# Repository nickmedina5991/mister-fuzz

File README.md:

# Mister Fuzz - Silicon Fuzz Face Guitar Pedal

A silicon Fuzz Face guitar effects pedal designed end-to-end:
LTSpice simulation, breadboard prototype, custom KiCad PCB, and a
custom Fusion 360 enclosure.

## What this is

A classic Fuzz Face circuit rebuilt with modern 2N3904 NPN silicon
transistors instead of the original 1960s germanium PNPs. The substitution
required re-deriving the bias network for silicon's higher hFE, since the
original 8.2kΩ bias resistor leaves Q2's collector at the wrong operating
point with modern transistors. The production design uses a 10kΩ trim pot
in place of the fixed resistor, so each build can be tuned to the specific
2N3904s installed.

## Features

- 9V battery or 2.1mm DC barrel jack power, with automatic switchover
- TRS input jack that disconnects the battery when no cable is plugged in
- 1N4001 reverse-polarity protection diode
- 47µF supply decoupling capacitor
- 3PDT true-bypass switching with LED indicator
- 10kΩ bias trimmer (set Q2 collector to 4.5V during assembly)
- 500kΩ audio-taper volume control
- 1kΩ linear fuzz control
- Two-layer PCB with stitched ground pour for low-noise high-gain operation

## Repo layout

- `simulation/` contains the LTSpice schematic and plots from the analysis
- `hardware/` contains the KiCad project, schematic and PCB exports, Gerbers, and BOM
- `docs/` contains the design notes and bias tuning instructions
- `enclosure/` will contain the Fusion 360 enclosure model and drill template (coming soon)

## Design highlights

The full design walkthrough lives in [`docs/design-notes.md`](docs/design-notes.md).
Some of the more interesting findings:

- **The silicon variant required ~6kΩ bias resistance instead of the original
  8.2kΩ.** A parametric LTSpice sweep of R3 from 2kΩ to 10kΩ identified the
  value that lands Q2's collector at the target 4.5V with modern 2N3904s.
- **The circuit has approximately 62dB of peak passband gain.** At realistic
  guitar signal levels (~200mV), the pedal saturates fully at any fuzz setting
  above the lowest 10% of the pot's range. This is why the Fuzz Face cleans
  up so dramatically when you roll back the guitar's volume knob.
- **The fuzz control sculpts EQ, not just gain.** At maximum fuzz, the
  response shows a resonant peak at 115Hz (in the guitar's low fundamental
  range). At minimum fuzz, the response flattens into a near-clean wideband
  amplifier. The pot changes both gain and tonal character simultaneously.
- **Simulation results match published ElectroSmash reference data** within
  the expected silicon-vs-germanium tolerances. The silicon variant has a
  slightly higher low-frequency corner (~50-80Hz vs 14Hz for germanium),
  which matches the documented "less bass" character of silicon Fuzz Faces.

## Build

1. Order parts per `hardware/bom.csv`.
2. Send `hardware/gerbers/mister-fuzz-gerbers.zip` to a PCB fab house
   (JLCPCB, PCBWay, OSH Park, etc.).
3. Hand-solder all through-hole components.
4. Wire the panel-mounted parts (audio jacks, footswitch, DC jack, LED)
   to the PCB pad headers using hookup wire.
5. Set the bias trim pot per [`docs/bias-tuning.md`](docs/bias-tuning.md).
6. Install in the enclosure and play.

## License

MIT. See [`LICENSE`](LICENSE) for details. You're free to use, modify,
build, and sell this design with attribution.

## Acknowledgments

- ElectroSmash's Fuzz Face analysis at
  [electrosmash.com/fuzz-face](https://www.electrosmash.com/fuzz-face)
  for the canonical reference data this design was verified against.
- R.G. Keen's "The Technology of the Fuzz Face" on GEOFEX for the
  background on bias sensitivity and transistor selection.
- Barbarach's website and tutorials on designing and building a 
  Fuzz Face clone (https://barbarach.com/articles/building-a-fuzz-face-clone/)
- Dallas Arbiter and the original 1966 Fuzz Face designers, whose
  deceptively simple two-transistor circuit has kept guitarists and
  electronics hobbyists busy for nearly 60 years.

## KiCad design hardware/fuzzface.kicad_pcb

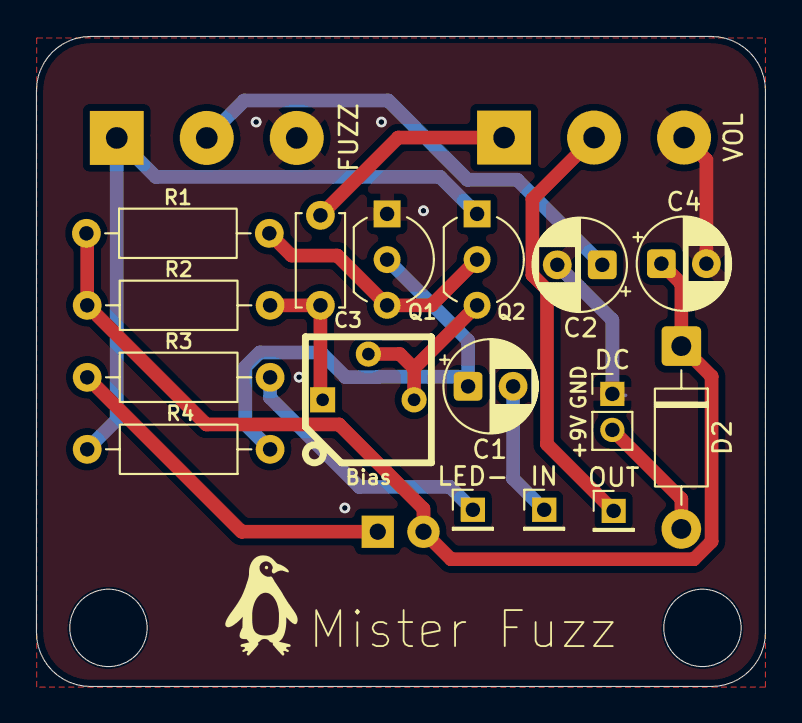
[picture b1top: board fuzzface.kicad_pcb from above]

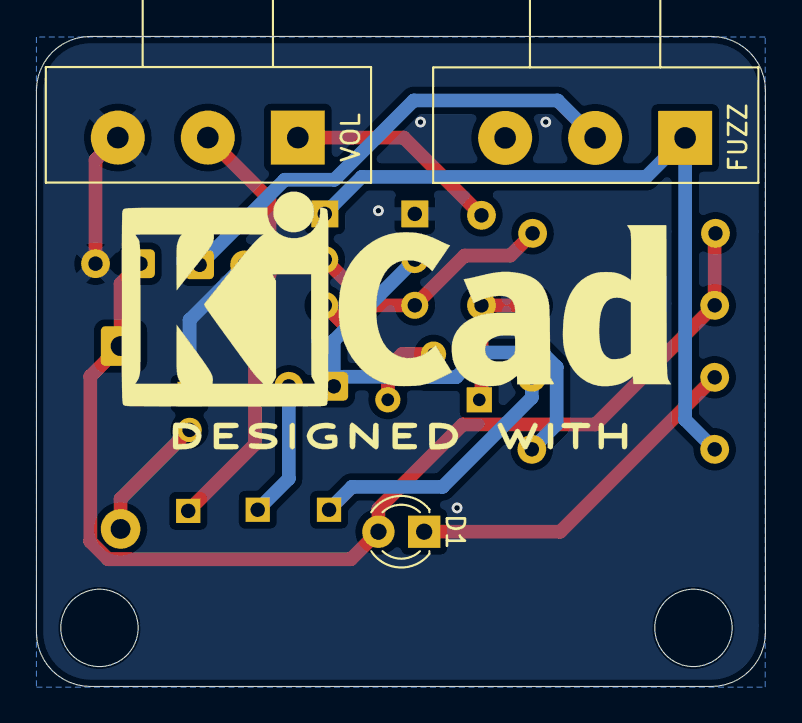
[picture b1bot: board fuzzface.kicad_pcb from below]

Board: 2 copper layers, 40.5 x 36.1 mm, 22 parts (6 on the bottom side), 14 nets.

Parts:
Bias: 10K; BOURNS-3362P_pot
C1: 2.2u; CP_Radial_D5.0mm_P2.50mm
C2: 22u; CP_Radial_D5.0mm_P2.50mm
C3: 0.01u; C_Disc_D5.0mm_W2.5mm_P5.00mm
C4: 47u; CP_Radial_D5.0mm_P2.50mm
D1: LED; LED_D3.0mm
D2: 1N4001; D_DO-41_SOD81_P10.16mm_Horizontal
H3, H4: MountingHole; MountingHole_4.3mm_M4
J1: IN; PinHeader_1x01_P2.00mm_Vertical
J2: OUT; PinHeader_1x01_P2.00mm_Vertical
J3: DC; PinHeader_1x02_P2.00mm_Vertical
J4: LED-; PinHeader_1x01_P2.00mm_Vertical
N1: Housing; KiCad-Logo2_12mm_SilkScreen
Q1, Q2: 2N3904; TO-92_Inline_Wide
R1: 33K; R_Axial_DIN0207_L6.3mm_D2.5mm_P10.16mm_Horizontal
R2: 470; R_Axial_DIN0207_L6.3mm_D2.5mm_P10.16mm_Horizontal
R3: 4.7k; R_Axial_DIN0207_L6.3mm_D2.5mm_P10.16mm_Horizontal
R4: 100K; R_Axial_DIN0207_L6.3mm_D2.5mm_P10.16mm_Horizontal
RV1: B1K; Potentiometer_Alps_RK163_Single_Horizontal
VOL: A500K; Potentiometer_Alps_RK163_Single_Horizontal

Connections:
+9V: C4.1, D1.2 (A), D2.1 (K), R1.1, R2.1
/IN: C1.2, J1.1
/OUT: J2.1, VOL.2
GND: C2.2, C4.2, J3.1, Q1.1 (E), RV1.3, VOL.3
unnamed: C2.1, RV1.2
unnamed: Bias.1, C3.1, R2.2
unnamed: C3.2, VOL.1
unnamed: D1.1 (K), R3.1
unnamed: D2.2 (A), J3.2
unnamed: J4.1 (Pin_1_1), R3.2
unnamed: C1.1, Q1.2 (B), R4.1
unnamed: Q1.3 (C), Q2.2 (B), R1.2
unnamed: Bias.2, Bias.3, Q2.3 (C)
unnamed: Q2.1 (E), R4.2, RV1.1

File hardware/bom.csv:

"Reference","Qty","Value","DNP","Exclude from BOM","Exclude from Board","Footprint","Datasheet"
"BT1","1","9V_Battery","","","","",""
"C1","1","2.2u","","","","Capacitor_THT:CP_Radial_D5.0mm_P2.50mm",""
"C2","1","22u","","","","Capacitor_THT:CP_Radial_D5.0mm_P2.50mm",""
"C3","1","0.01u","","","","Capacitor_THT:C_Disc_D5.0mm_W2.5mm_P5.00mm",""
"C4","1","47u","","","","Capacitor_THT:CP_Radial_D5.0mm_P2.50mm",""
"D1","1","LED","","","","LED_THT:LED_D3.0mm",""
"D2","1","1N4001","","","","Diode_THT:D_DO-41_SOD81_P10.16mm_Horizontal","http://www.vishay.com/docs/88503/1n4001.pdf"
"J1","1","IN","","","","Connector_PinHeader_2.00mm:PinHeader_1x01_P2.00mm_Vertical",""
"J2","1","OUT","","","","Connector_PinHeader_2.00mm:PinHeader_1x01_P2.00mm_Vertical",""
"J3","1","DC","","","","Connector_PinHeader_2.00mm:PinHeader_1x02_P2.00mm_Vertical",""
"J4","1","LED-","","","","Connector_PinHeader_2.00mm:PinHeader_1x01_P2.00mm_Vertical",""
"Q1,Q2","2","2N3904","","","","Package_TO_SOT_THT:TO-92_Inline_Wide","https://www.onsemi.com/pub/Collateral/2N3903-D.PDF"
"R1","1","33K","","","","Resistor_THT:R_Axial_DIN0207_L6.3mm_D2.5mm_P10.16mm_Horizontal",""
"R2","1","470","","","","Resistor_THT:R_Axial_DIN0207_L6.3mm_D2.5mm_P10.16mm_Horizontal",""
"R3","1","4.7k","","","","Resistor_THT:R_Axial_DIN0207_L6.3mm_D2.5mm_P10.16mm_Horizontal",""
"R4","1","100K","","","","Resistor_THT:R_Axial_DIN0207_L6.3mm_D2.5mm_P10.16mm_Horizontal",""
"RV1","1","B1K","","","","Potentiometer_THT:Potentiometer_Alps_RK163_Single_Horizontal",""
"RV2","1","A500K","","","","Potentiometer_THT:Potentiometer_Alps_RK163_Single_Horizontal",""
"RV3","1","10K","","","","MyLibrary:BOURNS-3362P_pot",""

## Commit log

2026-06-20 Added README and Documentation
2026-06-20 uploaded LTSpice sim files and images
2026-06-20 Added kicad hardware files and images
2026-06-20 uploaded bom
2026-06-23 uploaded gerber files
